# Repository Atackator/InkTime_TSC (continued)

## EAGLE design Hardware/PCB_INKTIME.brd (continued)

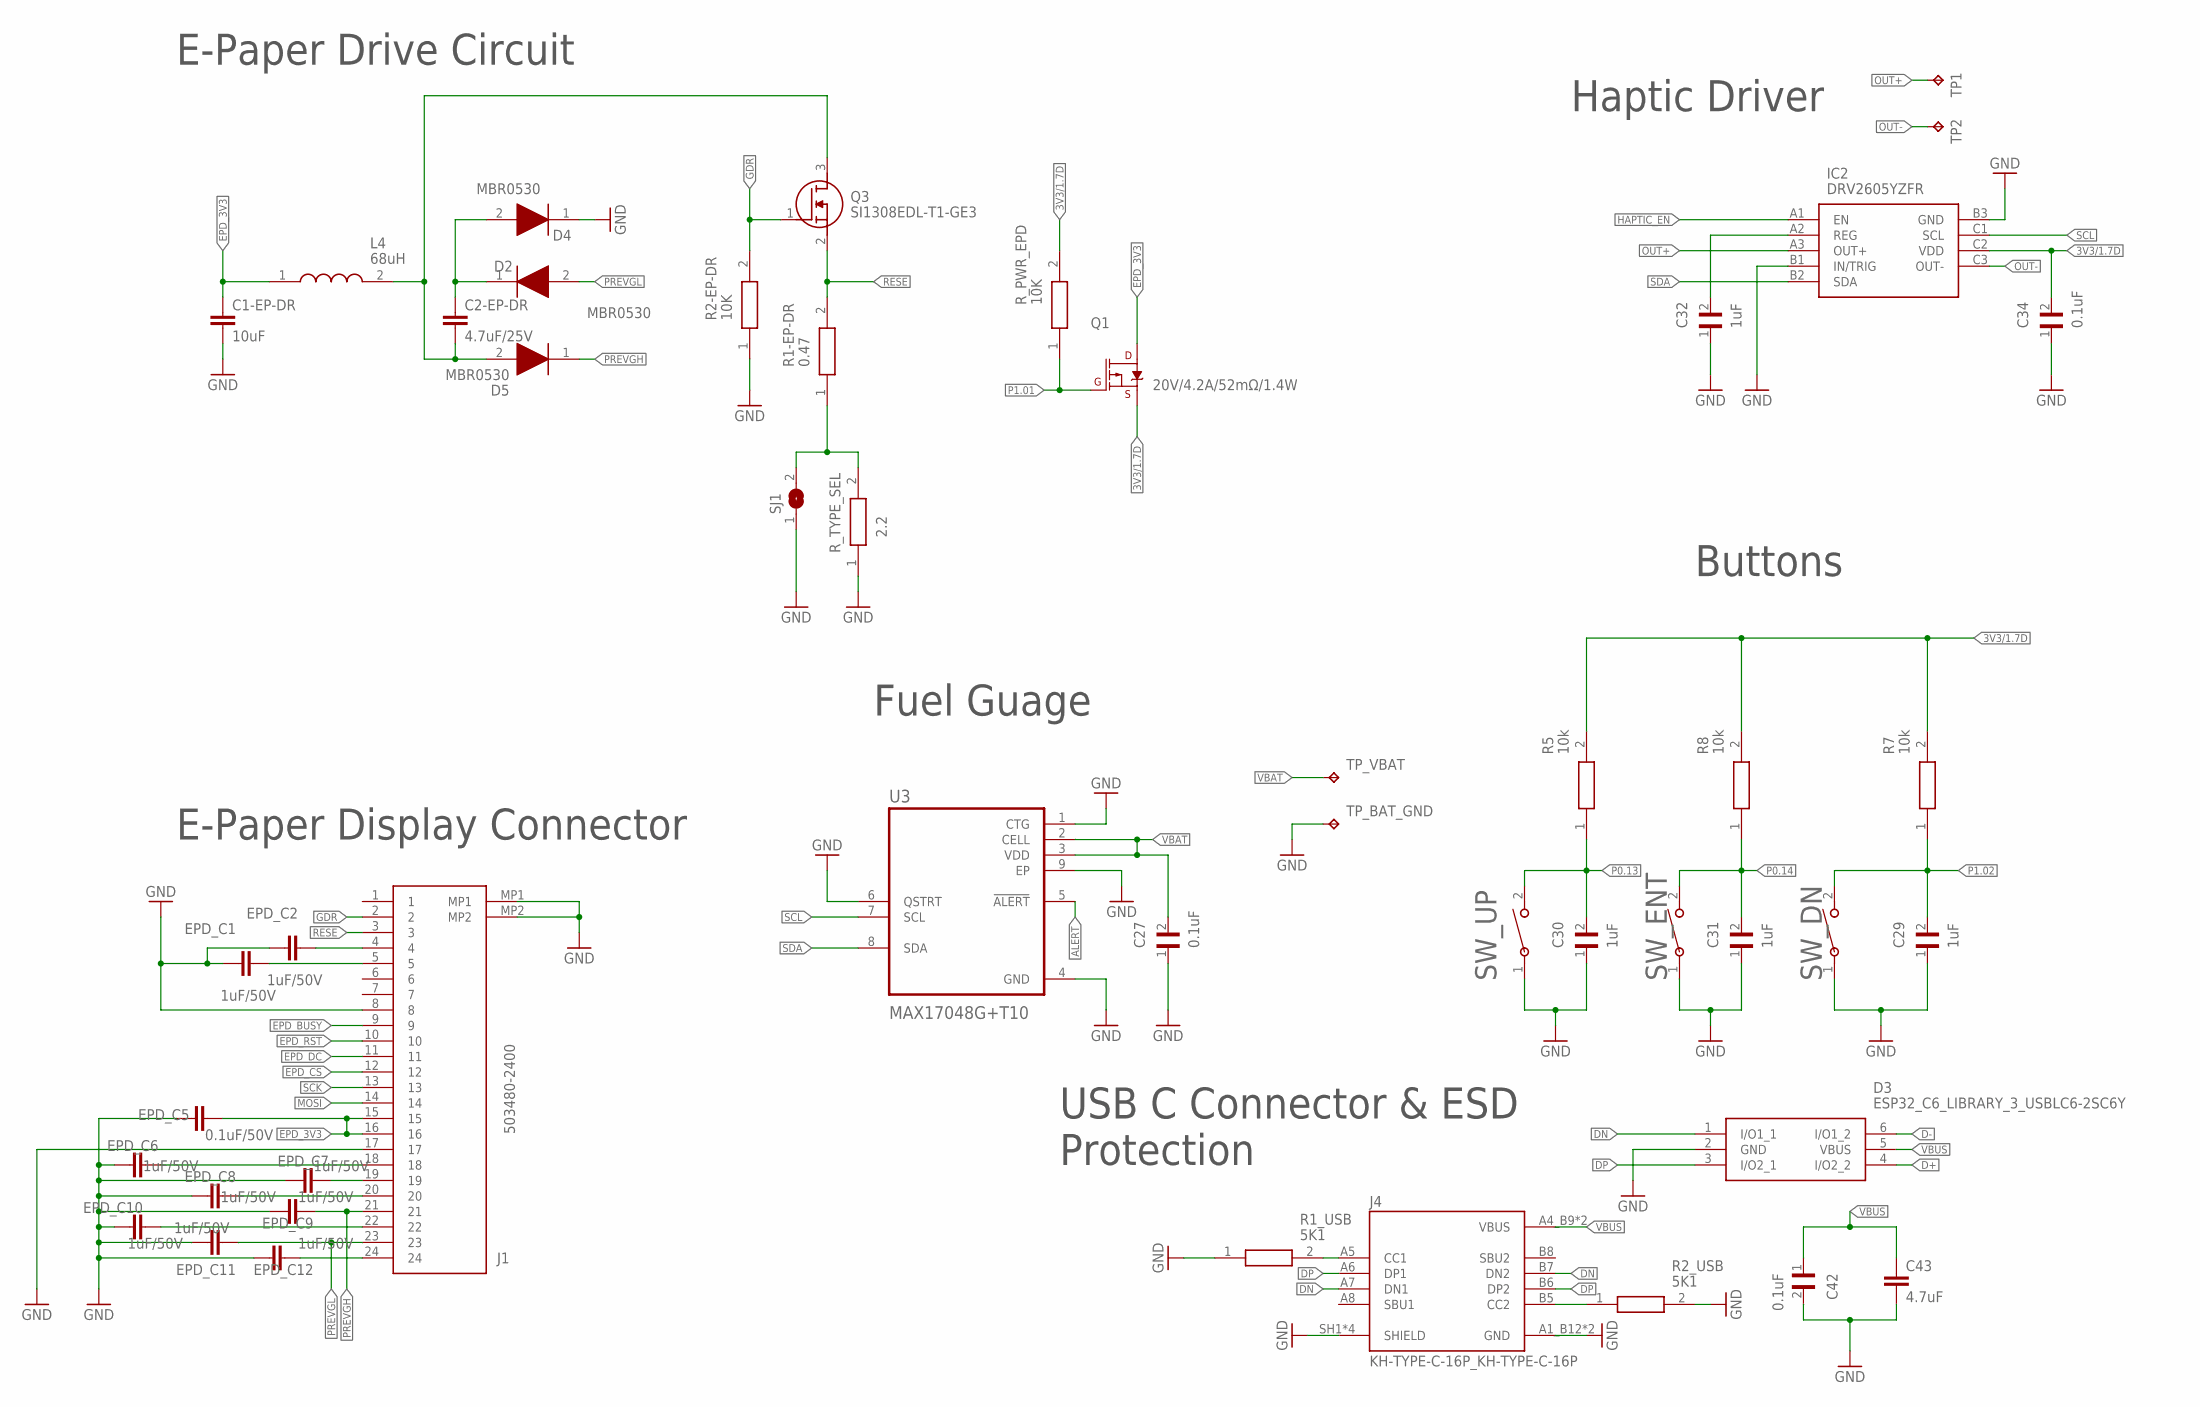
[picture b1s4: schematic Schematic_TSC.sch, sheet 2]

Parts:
C1-EP-DR: 10uF; NORDIC_NRF_3_RESC0201_L
C2-EP-DR: 4.7uF/25V; NORDIC_NRF_3_RESC0201_L
C27, C34, C42: 0.1uF; GRM011R60J152KE01L_2_CAPC0201X13N
C29, C30, C31, C32: 1uF; GRM011R60J152KE01L_2_CAPC0201X13N
C43: 4.7uF; NORDIC_NRF_3_RESC0201_L
D2, D4, D5: MBR0530; ESP32_C6_LIBRARY_5_SOD3716X135N
D3: ESP32_C6_LIBRARY_3_USBLC6-2SC6Y; ESP32_C6_LIBRARY_3_SOT95P280X145-6N
EPD_C1, EPD_C2, EPD_C6, EPD_C7, EPD_C8, EPD_C9, EPD_C10, EPD_C11, EPD_C12: 1uF/50V; NORDIC_NRF_3_RESC0201_L
EPD_C5: 0.1uF/50V; NORDIC_NRF_3_RESC0201_L
IC2: DRV2605YZFR; DRV2605YZFR_BGA9C50P3X3_144X144X62
J1: 503480-2400; 503480-2400_5034802400
J4: KH-TYPE-C-16P_KH-TYPE-C-16P; KH-TYPE-C-16P_KINGHELM_KH-TYPE-C-16P
L4: 68uH; MLP2016SR47MT0S1_INDC2016X100N
Q1: 20V/4.2A/52mΩ/1.4W; ESP32_C6_LIBRARY_4_ESP32_C6_LIBRARY_4_ESP32_C6_LIBRARY_4_ES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
Q3: SI1308EDL-T1-GE3; ESP32_C6_LIBRARY_6_SOT65P210X110-3N
R1-EP-DR: 0.47; CPF0201D7K68C1_0201
R1_USB, R2_USB: 5K1; CPF0201D7K68C1_0201
R2-EP-DR: 10K; CPF0201D7K68C1_0201
R5, R7, R8: 10k; CPF0201D7K68C1_0201
R_PWR_EPD: 10K; CPF0201D7K68C1_0201
R_TYPE_SEL: 2.2; CPF0201D7K68C1_0201
SJ1: ESP32_C6_LIBRARY_7_JUMPER_SJ
SW_DN: 2025-10-22_07-23-44_LIBRARY_EVP-AKE31ASW_EVP-AKE3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; 2025-10-22_07-23-44_LIBRARY_SW_EVP-AKE31A_PAN
SW_ENT: 2025-10-22_07-23-44_LIBRARY_EVP-AKE31ASW_EVP-AKE3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; 2025-10-22_07-23-44_LIBRARY_SW_EVP-AKE31A_PAN
SW_UP: 2025-10-22_07-23-44_LIBRARY_EVP-AKE31ASW_EVP-AKE3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; 2025-10-22_07-23-44_LIBRARY_SW_EVP-AKE31A_PAN
TP1, TP2: HECTOR_WATCH_1_TPTP20R; HECTOR_WATCH_1_TP20R
TP_BAT_GND: HECTOR_WATCH_1_TPTP20R; HECTOR_WATCH_1_TP20R
TP_VBAT: HECTOR_WATCH_1_TPTP20R; HECTOR_WATCH_1_TP20R
U3: MAX17048G+T10; ESP32_C6_LIBRARY_SON50P200X200X80-9N

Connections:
3V3/1.7D: C34.2, IC2.C2 (VDD), Q1.2 (S), R5.2, R7.2, R8.2, R_PWR_EPD.2
ALERT: U3.5 (!ALERT); also elsewhere on the board
D+: D3.4 (I/O2_2); also elsewhere on the board
D-: D3.6 (I/O1_2); also elsewhere on the board
DN: D3.1 (I/O1_1), J4.A7 (DN1), J4.B7 (DN2)
DP: D3.3 (I/O2_1), J4.A6 (DP1), J4.B6 (DP2)
EPD_3V3: C1-EP-DR.1, EPD_C5.2, J1.15, J1.16, L4.1, Q1.3 (D); also elsewhere on the board
EPD_BUSY: J1.9; also elsewhere on the board
EPD_CS: J1.12; also elsewhere on the board
EPD_DC: J1.11; also elsewhere on the board
EPD_RST: J1.10; also elsewhere on the board
GDR: J1.2, Q3.1 (G), R2-EP-DR.2
GND: C1-EP-DR.2, C27.1, C29.1, C30.1, C31.1, C32.1, C34.1, C42.2, C43.2, D3.2 (GND), D4.1 (K), EPD_C1.1, EPD_C2.1, EPD_C5.1, EPD_C6.1, EPD_C7.1, EPD_C8.1, EPD_C9.1, EPD_C10.1, EPD_C11.1, EPD_C12.1, IC2.B1 (IN/TRIG), IC2.B3 (GND), J1.8, J1.17, J1.MP1, J1.MP2, J4.A1_B12 (GND), J4.A12_B1 (GND), J4.SH1 (SHIELD), J4.SH2 (SHIELD), J4.SH3 (SHIELD), J4.SH4 (SHIELD), R1_USB.1, R2-EP-DR.1, R2_USB.2, R_TYPE_SEL.1, SJ1.1, SW_DN.1, SW_ENT.1, SW_UP.1, TP_BAT_GND.TP, U3.1 (CTG), U3.4 (GND), U3.6 (QSTRT), U3.9 (EP); also elsewhere on the board
HAPTIC_EN: IC2.A1 (EN); also elsewhere on the board
MOSI: J1.14; also elsewhere on the board
unnamed: C32.2, IC2.A2 (REG)
unnamed 36: C2-EP-DR.2, D5.2 (A), L4.2, Q3.3 (D); also elsewhere on the board
unnamed: C2-EP-DR.1, D2.1 (K), D4.2 (A)
unnamed: J4.A5 (CC1), R1_USB.2
unnamed: EPD_C2.2, J1.4
unnamed: R1-EP-DR.1, R_TYPE_SEL.2, SJ1.2
unnamed: EPD_C1.2, J1.5
unnamed: J4.B5 (CC2), R2_USB.1
unnamed: EPD_C6.2, J1.18
unnamed: EPD_C7.2, J1.19
unnamed: EPD_C8.2, J1.20
unnamed: EPD_C10.2, J1.22
unnamed: EPD_C12.2, J1.24
OUT+: IC2.A3 (OUT+), TP1.TP
OUT-: IC2.C3 (OUT-), TP2.TP
P0.13: C30.2, R5.1, SW_UP.2; also elsewhere on the board
P0.14: C31.2, R8.1, SW_ENT.2; also elsewhere on the board
P1.01: Q1.1 (G), R_PWR_EPD.1; also elsewhere on the board
P1.02: C29.2, R7.1, SW_DN.2; also elsewhere on the board
PREVGH: D5.1 (K), EPD_C9.2, J1.21
PREVGL: D2.2 (A), EPD_C11.2, J1.23
RESE: J1.3, Q3.2 (S), R1-EP-DR.2
SCK: J1.13; also elsewhere on the board
SCL: IC2.C1 (SCL), U3.7 (SCL); also elsewhere on the board
SDA: IC2.B2 (SDA), U3.8 (SDA); also elsewhere on the board
VBAT: C27.2, TP_VBAT.TP, U3.2 (CELL), U3.3 (VDD); also elsewhere on the board
VBUS: C42.1, C43.1, D3.5 (VBUS), J4.A4_B9 (VBUS), J4.A9_B4 (VBUS); also elsewhere on the board

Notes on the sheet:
E-Paper Drive Circuit
E-Paper Display Connector
Fuel Guage
Buttons
Haptic Driver
USB C Connector & ESD Protection

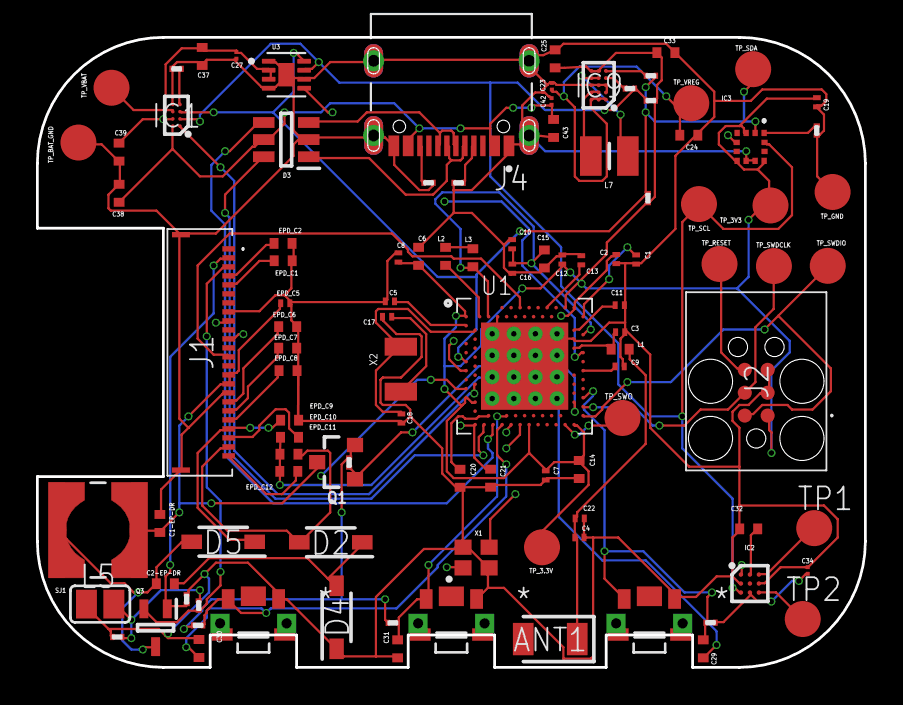
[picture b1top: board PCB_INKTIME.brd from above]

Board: 4 copper layers, 46.0 x 35.0 mm, 105 parts (0 on the bottom side), 71 nets.

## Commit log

2026-04-10 Update README.md
    Added a progress note to the README file.
2026-04-21 Revise README with project details and hardware overview
    Expanded project description and detailed hardware overview including components and functionalities.
2026-04-21 Add Bill of Materials to README
    Added a Bill of Materials section detailing components used in the InkTime-TSC project.
